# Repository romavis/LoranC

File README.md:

LORAN C (USSR "Chayka") receiver project
----

####Initial idea of project:
To build Loran-C navigational receiver with digital signal processing.  
Loran-C is (was?) a ground-based longwave navigational system working on frequency of 100 KHz, that was heavely used both by civilians and military prior to wide GPS adoption.

Receiver should also be able to lock onto signal of USSR "Chayka" system, similar to Loran-C, due to my location (nearest transmitter chain is "Chayka" GRI 8000)

####Licensed under:

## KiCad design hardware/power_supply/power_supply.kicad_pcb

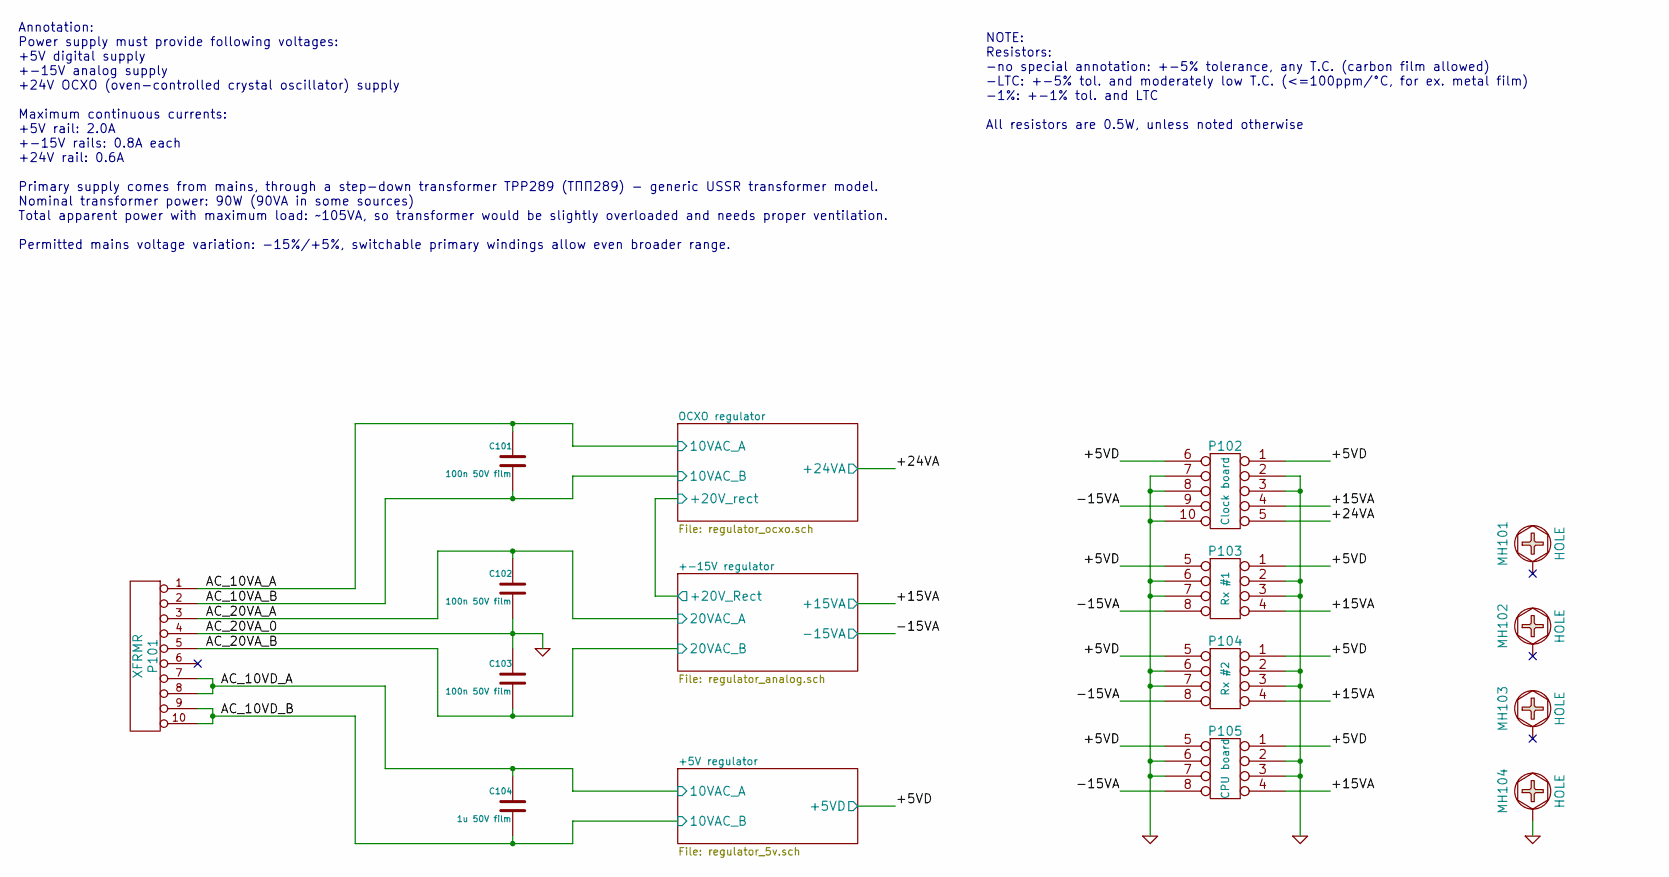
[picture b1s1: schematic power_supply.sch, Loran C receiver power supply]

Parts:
C101, C102, C103: 100n 50V film
C104: 1u 50V film
MH101, MH102, MH103, MH104: HOLE
P101: XFRMR
P102: Clock board
P103: Rx #1
P104: Rx #2
P105: CPU board

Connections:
/+5V regulator/10VAC_A: C104.1, P101.7, P101.8; also elsewhere on the board
/+5V regulator/10VAC_B: C104.2, P101.9, P101.10; also elsewhere on the board
/+5V regulator/+5VD: P102.1, P102.6, P103.1, P103.5, P104.1, P104.5, P105.1, P105.5; also elsewhere on the board
/+-15V regulator/20VAC_A: C102.1, P101.3; also elsewhere on the board
/+-15V regulator/20VAC_B: C103.2, P101.5; also elsewhere on the board
/+-15V regulator/+15VA: P102.4, P103.4, P104.4, P105.4; also elsewhere on the board
/+-15V regulator/-15VA: P102.9, P103.8, P104.8, P105.8; also elsewhere on the board
/OCXO regulator/10VAC_A: C101.1, P101.1; also elsewhere on the board
/OCXO regulator/10VAC_B: C101.2, P101.2; also elsewhere on the board
/OCXO regulator/+24VA: P102.5; also elsewhere on the board
GND: C102.2, C103.1, MH104.1, P101.4, P102.2, P102.3, P102.7, P102.8, P102.10, P103.2, P103.3, P103.6, P103.7, P104.2, P104.3, P104.6, P104.7, P105.2, P105.3, P105.6, P105.7; also elsewhere on the board

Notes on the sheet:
Annotation: Power supply must provide following voltages: +5V digital supply +-15V analog supply +24V OCXO (oven-controlled crystal oscillator) supply Maximum continuous currents: +5V rail: 2.0A +-15V rails: 0.8A each +24V rail: 0.6A Primary supply comes from mains, through a step-down transformer 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
NOTE: Resistors: -no special annotation: +-5% tolerance, any T.C. (carbon film allowed) -LTC: +-5% tol. and moderately low T.C. (<=100ppm/°C, for ex. metal film) -1%: +-1% tol. and LTC All resistors are 0.5W, unless noted otherwise

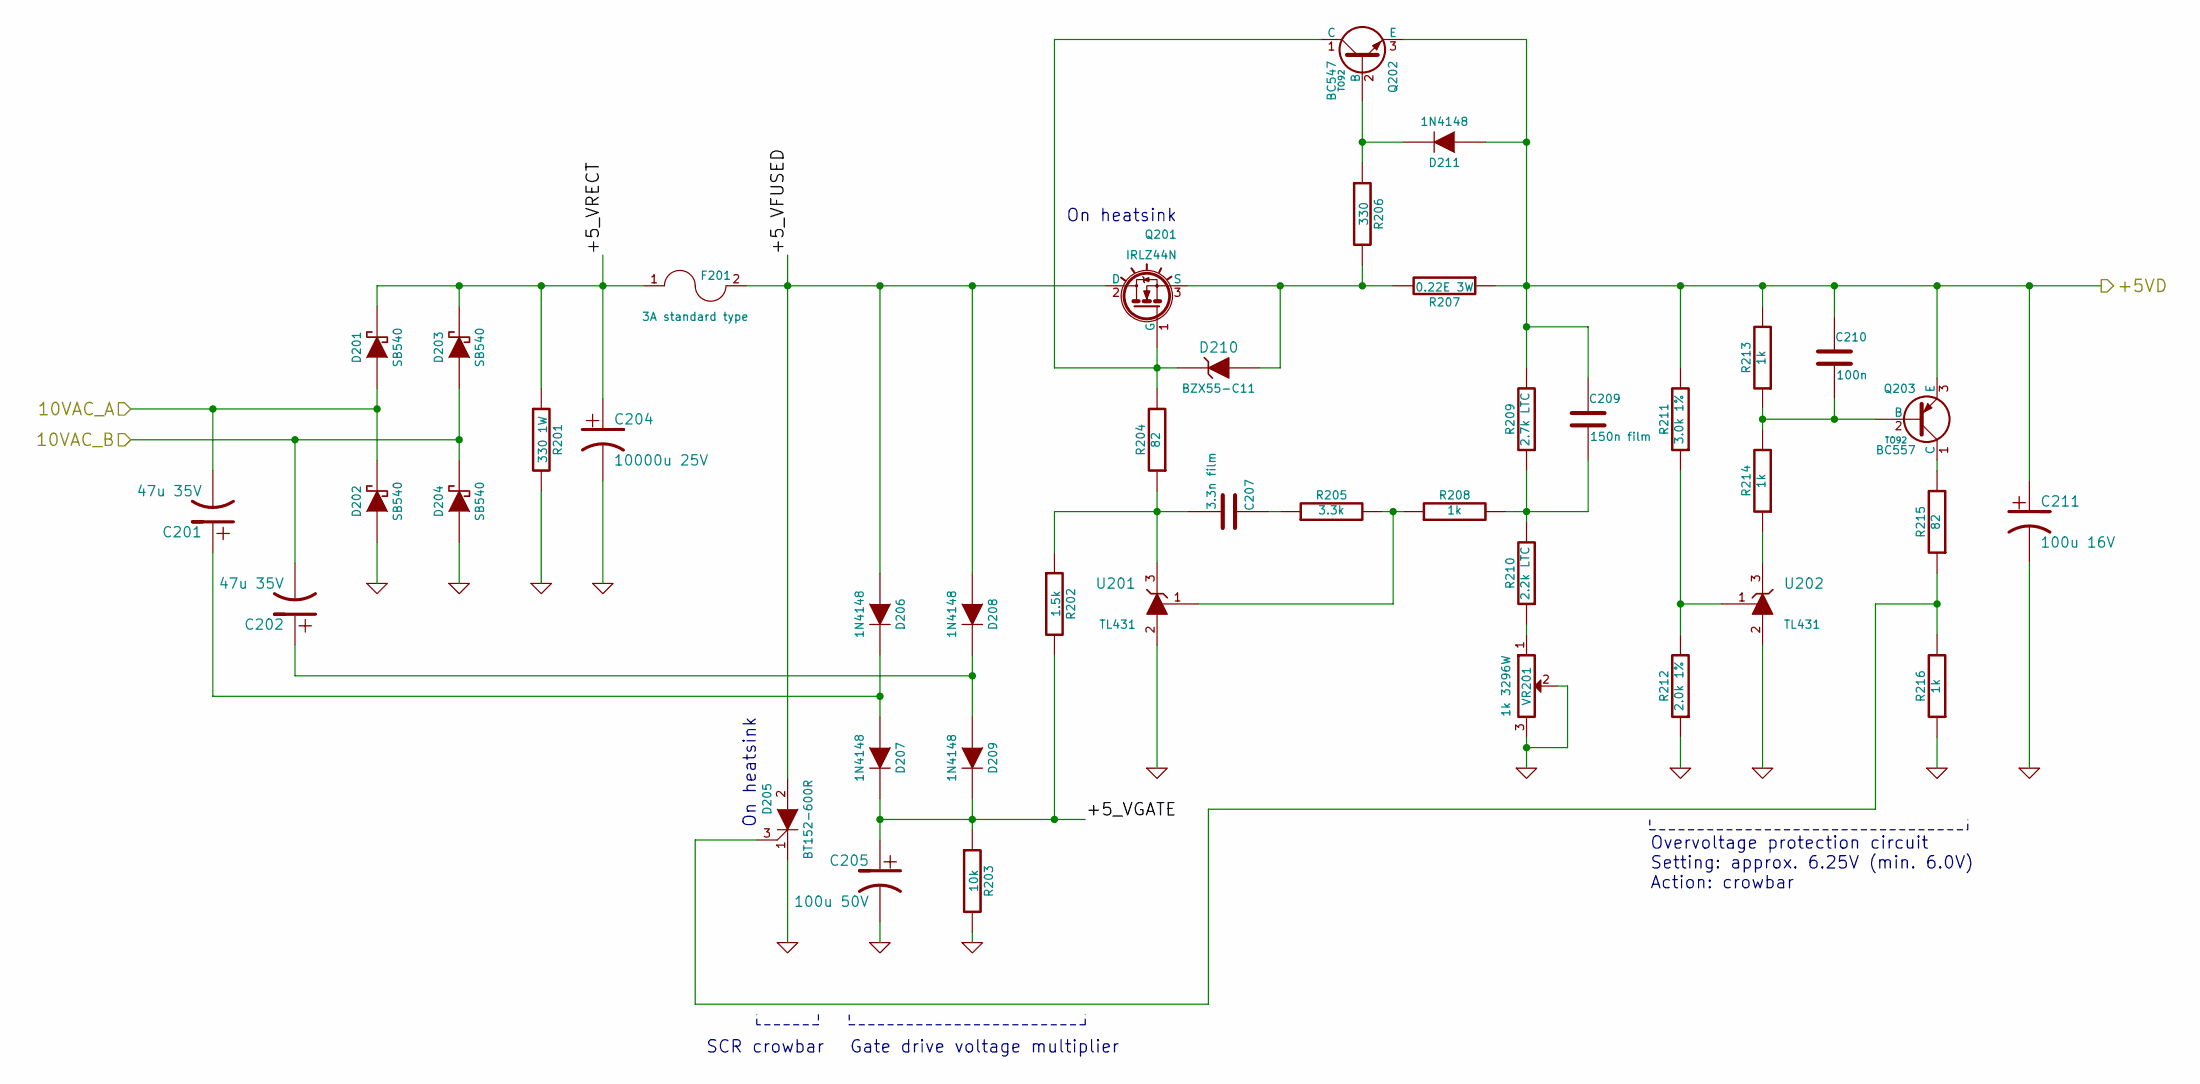
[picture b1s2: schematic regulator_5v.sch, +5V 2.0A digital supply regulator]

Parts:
C201, C202: 47u 35V
C204: 10000u 25V
C205: 100u 50V
C207: 3.3n film
C209: 150n film
C210: 100n
C211: 100u 16V
D201, D202, D203, D204: SB540
D205: BT152-600R
D206, D207, D208, D209, D211: 1N4148
D210: BZX55-C11
F201: 3A standard type
Q201: IRLZ44N
Q202: BC547; TO92
Q203: BC557; TO92
R201: 330 1W
R202: 1.5k
R203: 10k
R204, R215: 82
R205: 3.3k
R206: 330
R207: 0.22E 3W
R208, R213, R214, R216: 1k
R209: 2.7k LTC
R210: 2.2k LTC
R211: 3.0k 1%
R212: 2.0k 1%
U201, U202: TL431; TO92
VR201: 1k 3296W

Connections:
/+5V regulator/10VAC_A: C201.2, D201.1 (A), D202.2 (K); also elsewhere on the board
/+5V regulator/10VAC_B: C202.2, D203.1 (A), D204.2 (K); also elsewhere on the board
/+5V regulator/+5VD: C209.1, C210.1, C211.1, D211.1 (A), Q202.3 (E), Q203.3 (E), R207.1, R209.2, R211.2, R213.2; also elsewhere on the board
/+5V regulator/+5_VFUSED: D205.2 (A), D206.1 (A), D208.1 (A), F201.2, Q201.2 (D)
/+5V regulator/+5_VGATE: C205.1, D207.2 (K), D209.2 (K), R202.2, R203.1
/+5V regulator/+5_VRECT: C204.1, D201.2 (K), D203.2 (K), F201.1, R201.1
GND: C204.2, C205.2, C211.2, D202.1 (A), D204.1 (A), D205.1 (K), R201.2, R203.2, R212.1, R216.1, U201.2 (A), U202.2 (A), VR201.2, VR201.3; also elsewhere on the board
unnamed: C201.1, D206.2 (K), D207.1 (A)
unnamed: C202.1, D208.2 (K), D209.1 (A)
unnamed: C207.1, R205.1
unnamed: C207.2, R202.1, R204.1, U201.3 (K)
unnamed: C209.2, R208.2, R209.1, R210.2
unnamed: C210.2, Q203.2 (B), R213.1, R214.2
unnamed: D205.3 (G), R215.1, R216.2
unnamed: D210.1 (A), Q201.3 (S), R206.2, R207.2
unnamed: D210.2 (K), Q201.1 (G), Q202.1 (C), R204.2
unnamed: D211.2 (K), Q202.2 (B), R206.1
unnamed: Q203.1 (C), R215.2
unnamed: R205.2, R208.1, U201.1 (Ref)
unnamed: R210.1, VR201.1
unnamed: R211.1, R212.2, U202.1 (Ref)
unnamed: R214.1, U202.3 (K)

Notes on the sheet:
Overvoltage protection circuit Setting: approx. 6.25V (min. 6.0V) Action: crowbar
Gate drive voltage multiplier
SCR crowbar
On heatsink

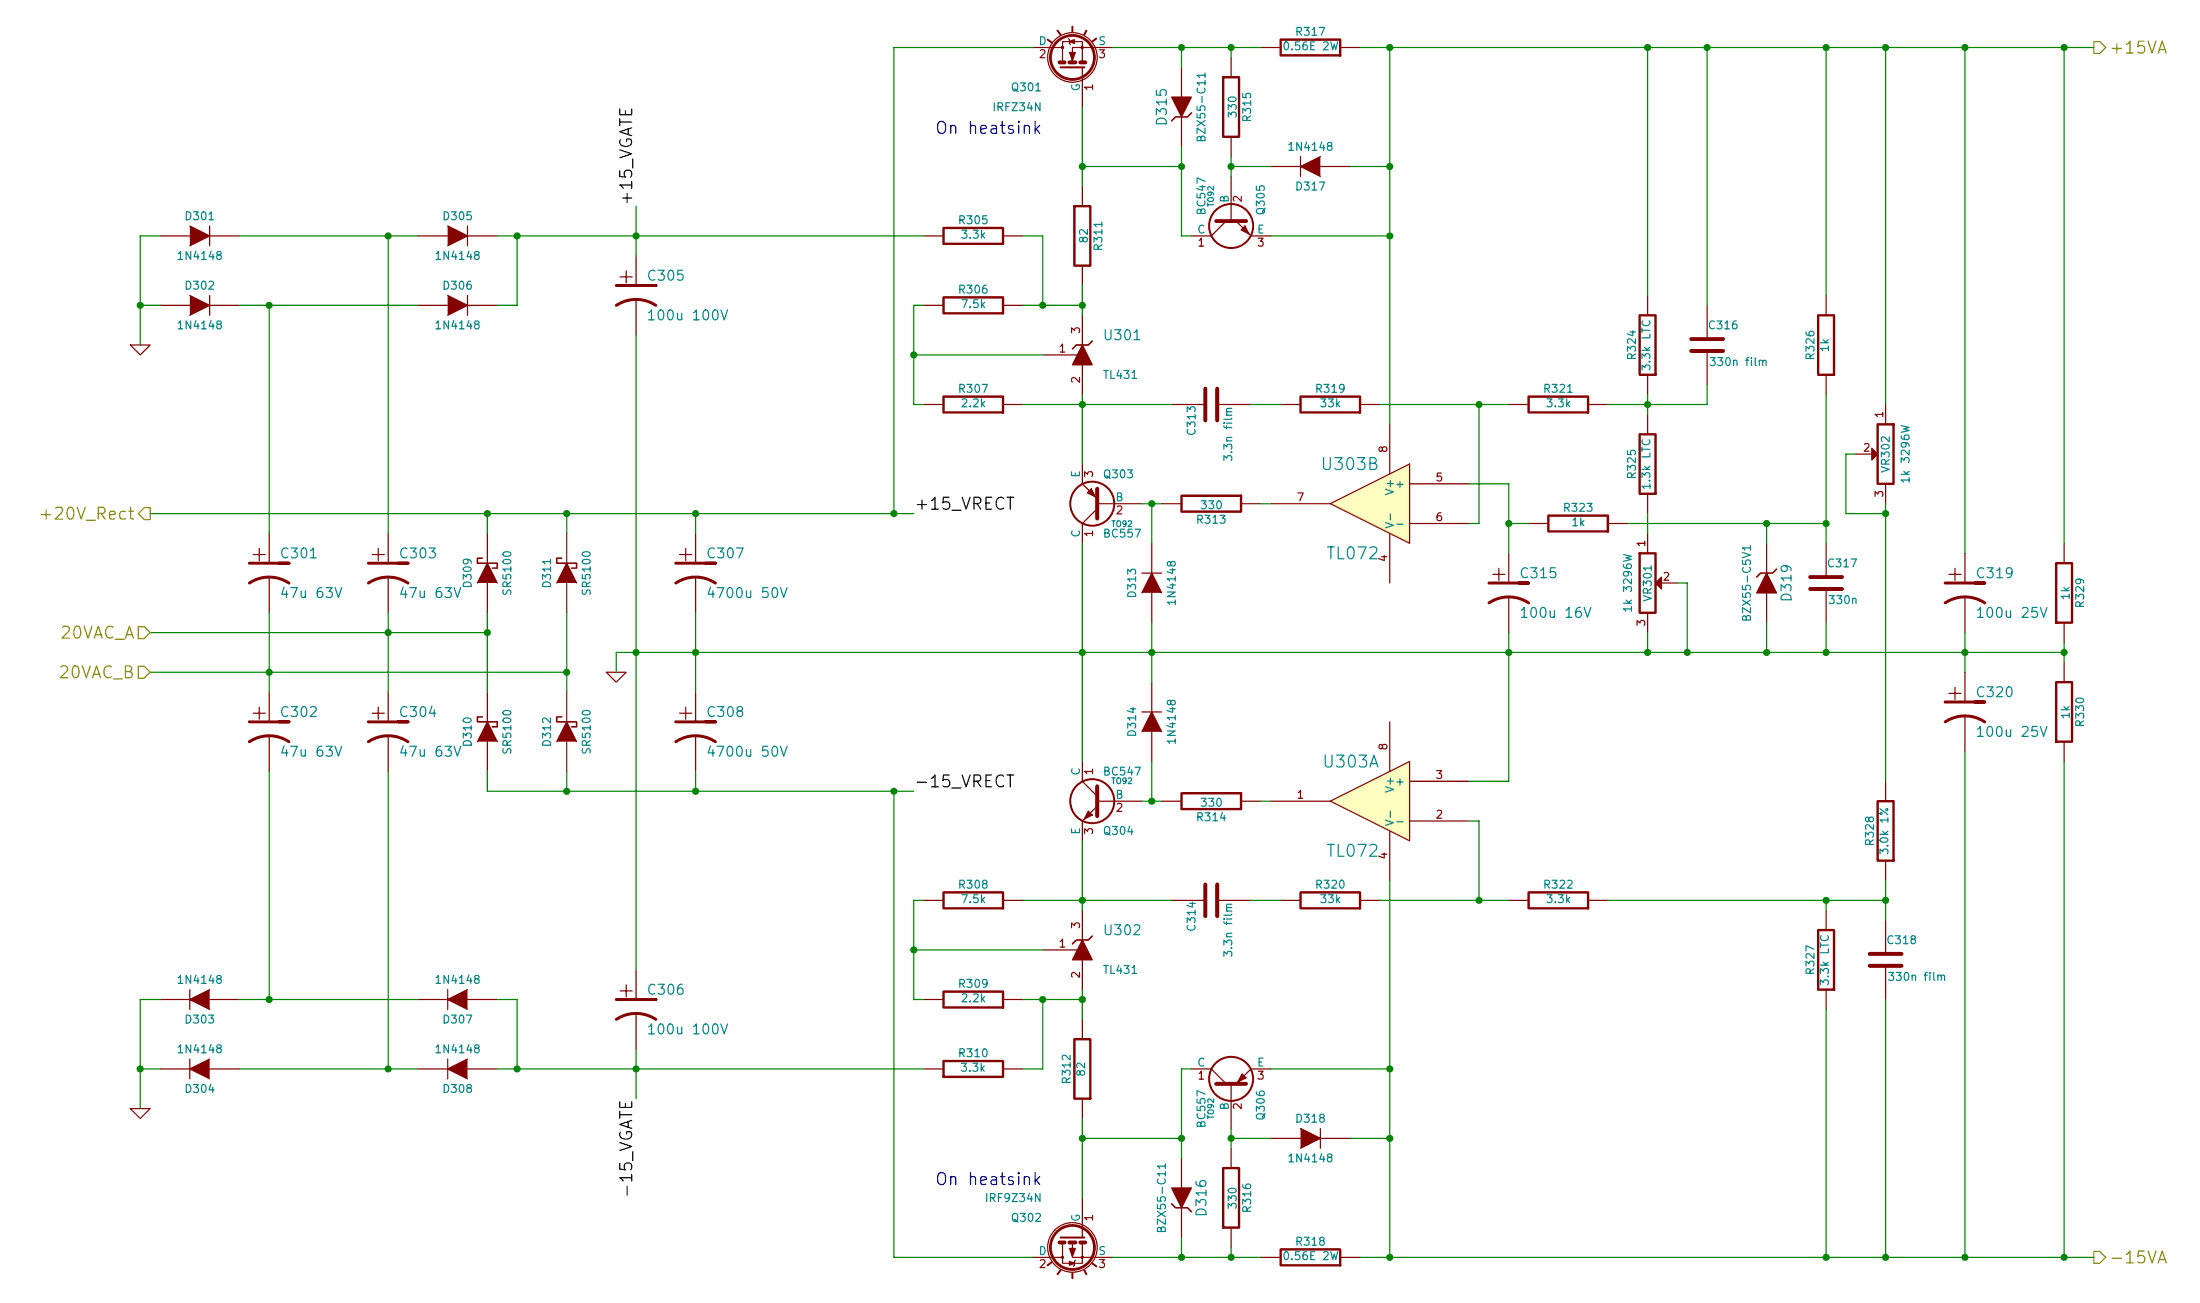
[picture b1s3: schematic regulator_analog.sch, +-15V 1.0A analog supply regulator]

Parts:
C301, C302, C303, C304: 47u 63V
C305, C306: 100u 100V
C307, C308: 4700u 50V
C313, C314: 3.3n film
C315: 100u 16V
C316, C318: 330n film
C317: 330n
C319, C320: 100u 25V
D301, D302, D303, D304, D305, D306, D307, D308, D313, D314, D317, D318: 1N4148
D309, D310, D311, D312: SR5100
D315, D316: BZX55-C11
D319: BZX55-C5V1
Q301: IRFZ34N
Q302: IRF9Z34N
Q303, Q306: BC557; TO92
Q304, Q305: BC547; TO92
R305, R310, R321, R322: 3.3k
R306, R308: 7.5k
R307, R309: 2.2k
R311, R312: 82
R313, R314, R315, R316: 330
R317, R318: 0.56E 2W
R319, R320: 33k
R323, R326, R329, R330: 1k
R324, R327: 3.3k LTC
R325: 1.3k LTC
R328: 3.0k 1%
U301, U302: TL431; TO92
U303: TL072
VR301, VR302: 1k 3296W

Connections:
/+-15V regulator/20VAC_A: C303.2, C304.1, D309.1 (A), D310.2 (K); also elsewhere on the board
/+-15V regulator/20VAC_B: C301.2, C302.1, D311.1 (A), D312.2 (K); also elsewhere on the board
/+-15V regulator/+15VA: C316.1, C319.1, D317.1 (A), Q305.3 (E), R317.1, R324.2, R326.2, R329.2, U303.8 (V+), VR302.1; also elsewhere on the board
/+-15V regulator/+15_VGATE: C305.1, D305.2 (K), D306.2 (K), R305.2
/+-15V regulator/+20V_Rect: C307.1, D309.2 (K), D311.2 (K), Q301.2 (D); also elsewhere on the board
/+-15V regulator/-15VA: C318.2, C320.2, D318.2 (K), Q306.3 (E), R318.1, R327.1, R330.1, U303.4 (V-); also elsewhere on the board
/+-15V regulator/-15_VGATE: C306.2, D307.1 (A), D308.1 (A), R310.1
/+-15V regulator/-15_VRECT: C308.2, D310.1 (A), D312.1 (A), Q302.2 (D)
GND: C305.2, C306.1, C307.2, C308.1, C315.2, C317.2, C319.2, C320.1, D301.1 (A), D302.1 (A), D303.2 (K), D304.2 (K), D313.1 (A), D314.2 (K), D319.1 (A), Q303.1 (C), Q304.1 (C), R329.1, R330.2, U303.3 (+), VR301.2, VR301.3; also elsewhere on the board
unnamed: C301.1, D302.2 (K), D306.1 (A)
unnamed: C302.2, D303.1 (A), D307.2 (K)
unnamed: C303.1, D301.2 (K), D305.1 (A)
unnamed: C304.2, D304.1 (A), D308.2 (K)
unnamed: C313.1, Q303.3 (E), R307.1, U301.2 (A)
unnamed: C313.2, R319.2
unnamed: C314.1, Q304.3 (E), R308.1, U302.3 (K)
unnamed: C314.2, R320.2
unnamed: C315.1, R323.2, U303.5 (+)
unnamed: C316.2, R321.1, R324.1, R325.2
unnamed: C317.1, D319.2 (K), R323.1, R326.1
unnamed: C318.1, R322.1, R327.2, R328.1
unnamed: D313.2 (K), Q303.2 (B), R313.2
unnamed: D314.1 (A), Q304.2 (B), R314.2
unnamed: D315.1 (A), Q301.3 (S), R315.1, R317.2
unnamed: D315.2 (K), Q301.1 (G), Q305.1 (C), R311.1
unnamed: D316.1 (A), Q302.1 (G), Q306.1 (C), R312.1
unnamed: D316.2 (K), Q302.3 (S), R316.1, R318.2
unnamed: D317.2 (K), Q305.2 (B), R315.2
unnamed: D318.1 (A), Q306.2 (B), R316.2
unnamed: R305.1, R306.1, R311.2, U301.3 (K)
unnamed: R306.2, R307.2, U301.1 (Ref)
unnamed: R308.2, R309.2, U302.1 (Ref)
unnamed: R309.1, R310.2, R312.2, U302.2 (A)
unnamed: R313.1, U303.7
unnamed: R314.1, U303.1
unnamed: R319.1, R321.2, U303.6 (-)
unnamed: R320.1, R322.2, U303.2 (-)
unnamed: R325.1, VR301.1
unnamed: R328.2, VR302.2, VR302.3

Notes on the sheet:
On heatsink

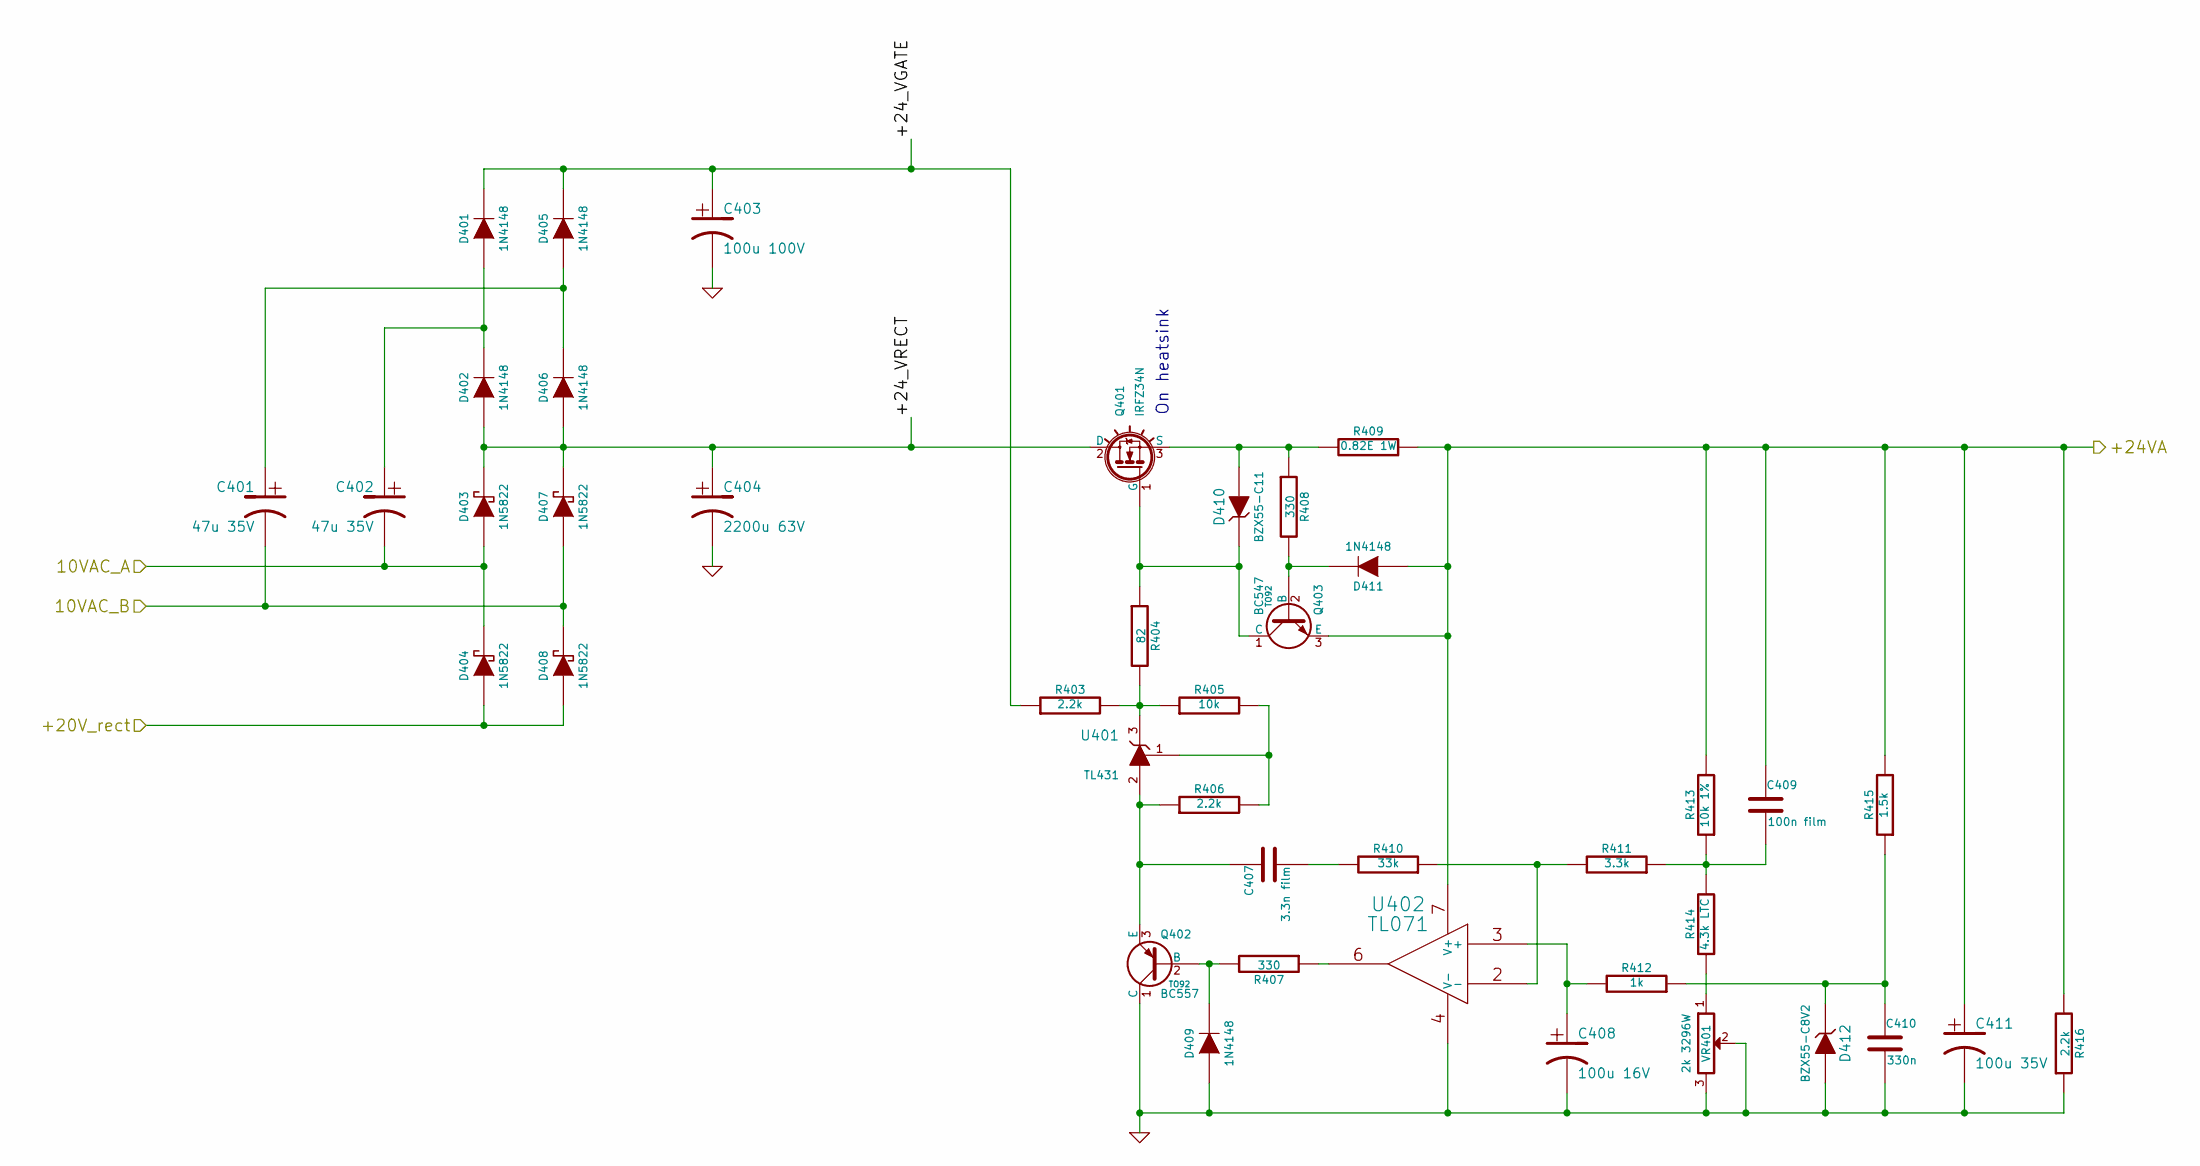
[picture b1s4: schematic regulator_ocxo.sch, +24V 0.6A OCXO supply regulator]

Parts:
C401, C402: 47u 35V
C403: 100u 100V
C404: 2200u 63V
C407: 3.3n film
C408: 100u 16V
C409: 100n film
C410: 330n
C411: 100u 35V
D401, D402, D405, D406, D409, D411: 1N4148
D403, D404, D407, D408: 1N5822
D410: BZX55-C11
D412: BZX55-C8V2
Q401: IRFZ34N
Q402: BC557; TO92
Q403: BC547; TO92
R403, R406, R416: 2.2k
R404: 82
R405: 10k
R407, R408: 330
R409: 0.82E 1W
R410: 33k
R411: 3.3k
R412: 1k
R413: 10k 1%
R414: 4.3k LTC
R415: 1.5k
U401: TL431; TO92
U402: TL071
VR401: 2k 3296W

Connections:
/+-15V regulator/+20V_Rect: D404.1 (A), D408.1 (A); also elsewhere on the board
/OCXO regulator/10VAC_A: C402.2, D403.1 (A), D404.2 (K); also elsewhere on the board
/OCXO regulator/10VAC_B: C401.2, D407.1 (A), D408.2 (K); also elsewhere on the board
/OCXO regulator/+24VA: C409.1, C411.1, D411.1 (A), Q403.3 (E), R409.1, R413.2, R415.2, R416.2, U402.7 (V+); also elsewhere on the board
/OCXO regulator/+24_VGATE: C403.1, D401.2 (K), D405.2 (K), R403.1
/OCXO regulator/+24_VRECT: C404.1, D402.1 (A), D403.2 (K), D406.1 (A), D407.2 (K), Q401.2 (D)
GND: C403.2, C404.2, C408.2, C410.2, C411.2, D409.1 (A), D412.1 (A), Q402.1 (C), R416.1, U402.4 (V-), VR401.2, VR401.3; also elsewhere on the board
unnamed: C401.1, D405.1 (A), D406.2 (K)
unnamed: C402.1, D401.1 (A), D402.2 (K)
unnamed: C407.1, Q402.3 (E), R406.1, U401.2 (A)
unnamed: C407.2, R410.2
unnamed: C408.1, R412.2, U402.3 (+)
unnamed: C409.2, R411.1, R413.1, R414.2
unnamed: C410.1, D412.2 (K), R412.1, R415.1
unnamed: D409.2 (K), Q402.2 (B), R407.2
unnamed: D410.1 (A), Q401.3 (S), R408.1, R409.2
unnamed: D410.2 (K), Q401.1 (G), Q403.1 (C), R404.1
unnamed: D411.2 (K), Q403.2 (B), R408.2
unnamed: R403.2, R404.2, R405.1, U401.3 (K)
unnamed: R405.2, R406.2, U401.1 (Ref)
unnamed: R407.1, U402.6
unnamed: R410.1, R411.2, U402.2 (-)
unnamed: R414.1, VR401.1

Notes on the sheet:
On heatsink

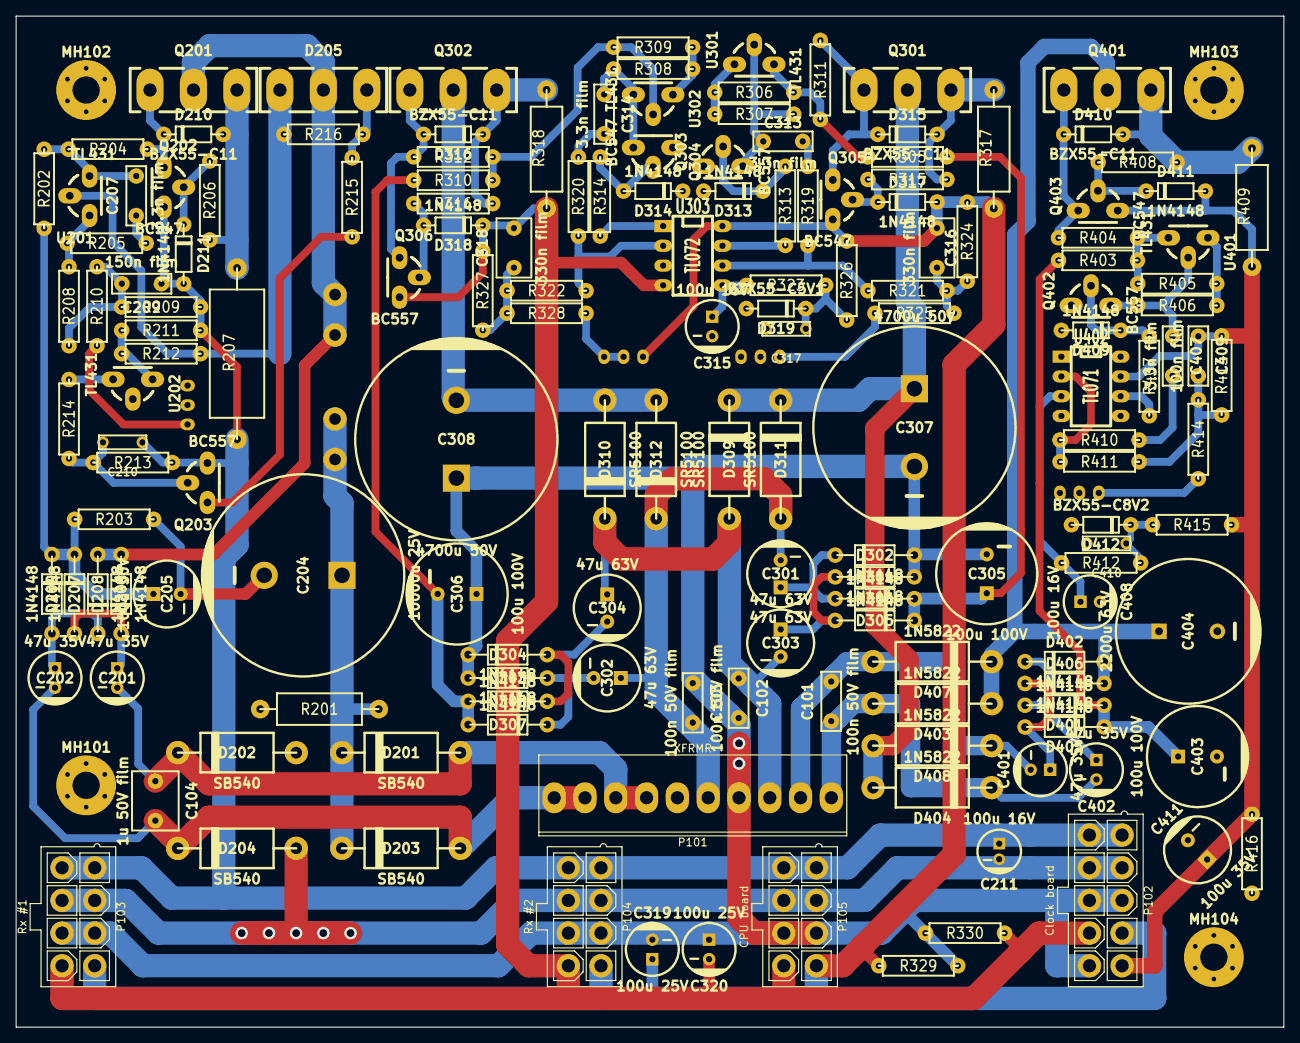
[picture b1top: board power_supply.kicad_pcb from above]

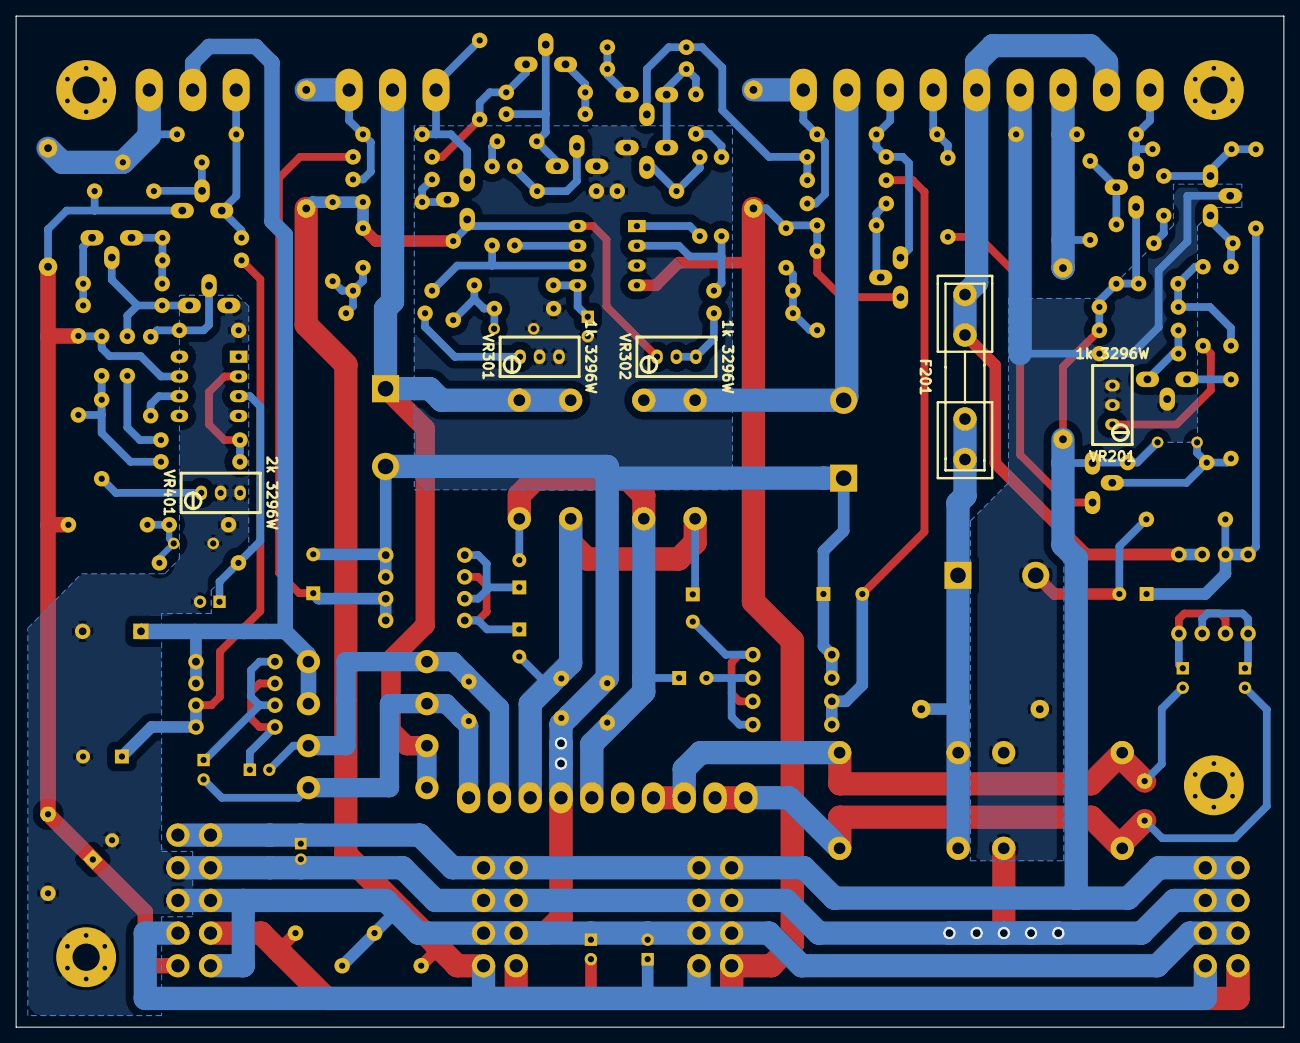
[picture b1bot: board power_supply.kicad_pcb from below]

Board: 2 copper layers, 163.0 x 130.0 mm, 168 parts (5 on the bottom side), 81 nets.

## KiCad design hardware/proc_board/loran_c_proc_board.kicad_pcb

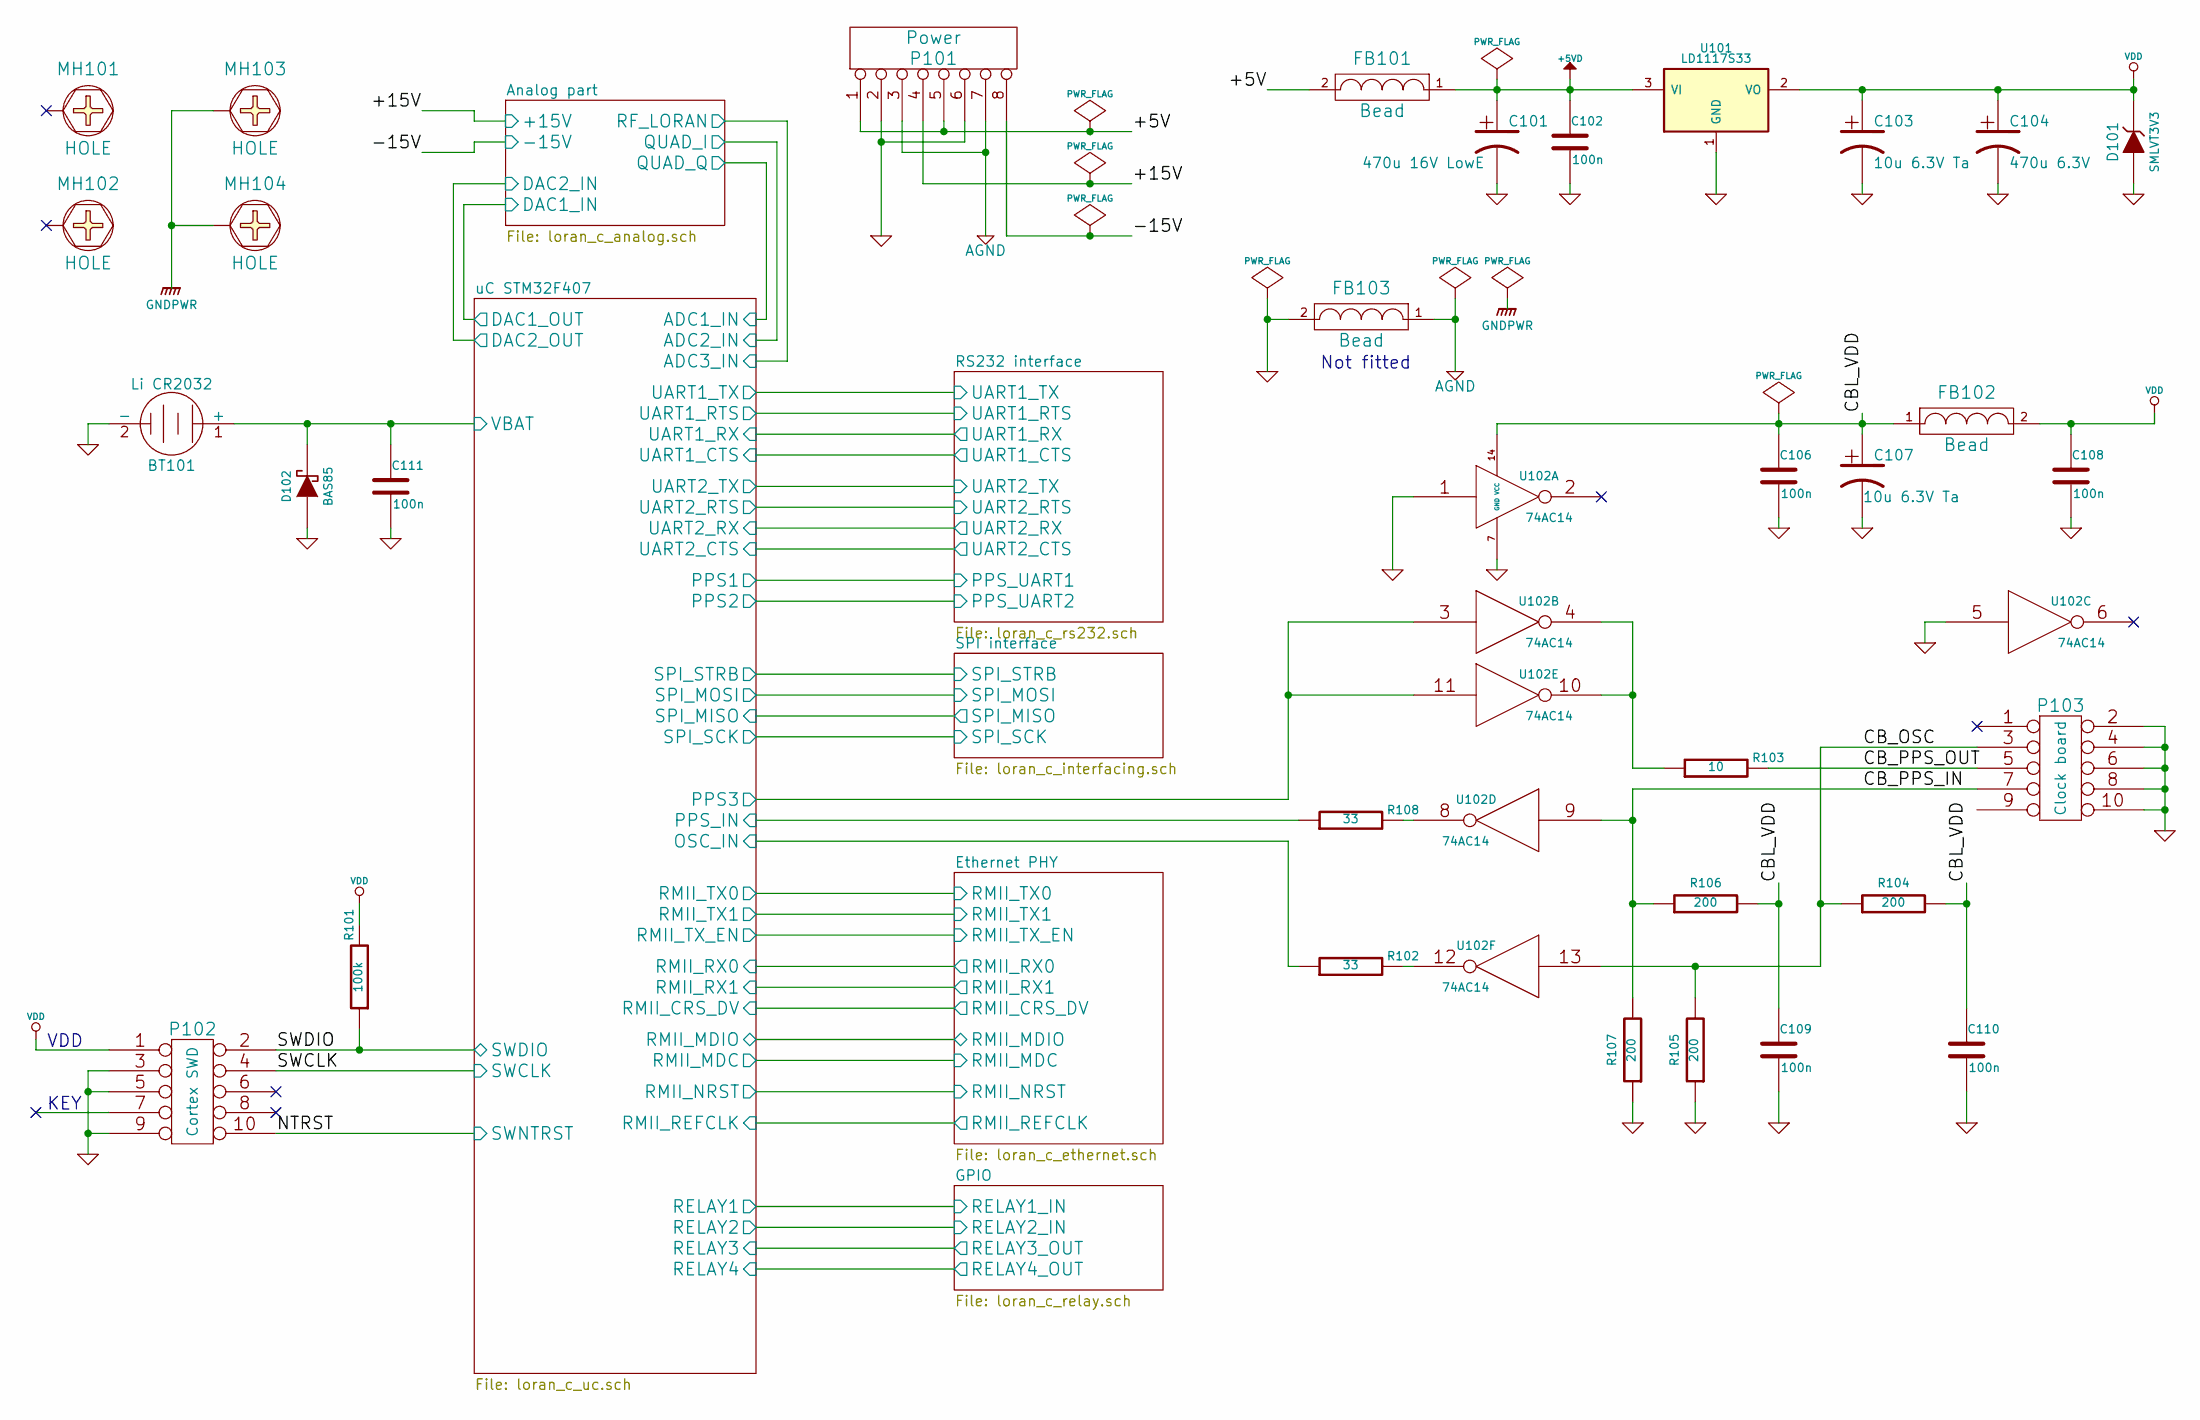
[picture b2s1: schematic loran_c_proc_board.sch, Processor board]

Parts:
BT101: Li CR2032; bh840
C101: 470u 16V LowE; CP_10x12.5mm
C102, C106, C108, C109, C110: 100n; c_1206
C103, C107: 10u 6.3V Ta; c_tant_B
C104: 470u 6.3V; CP_6.3x11mm
C111: 100n; c_0805
D101: SMLVT3V3; do214aa
D102: BAS85; sod80c
FB101: Bead; RC07
FB102: Bead; rc07_vert
FB103: Bead; SM1812E
MH101, MH102, MH103, MH104: HOLE; Hole_3-5mm
P101: Power; minifit-8
P102: Cortex SWD; vasch_strip_5x2
P103: Clock board; vasch_strip_5x2
R101: 100k; r_1206
R102, R108: 33; r_1206
R103: 10; r_1206
R104, R105, R106, R107: 200; r_1206
U101: LD1117S33; TO-220_Neutral123_Vertical
U102: 74AC14; so-14

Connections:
+5VD: C101.1, C102.1, FB101.1, U101.3 (VI); also elsewhere on the board
/+5V: FB101.2, P101.1, P101.5
/Analog part/+15V: P101.4; also elsewhere on the board
/Analog part/-15V: P101.8; also elsewhere on the board
/CBL_VDD: C106.1, C107.1, C109.1, C110.1, FB102.1, R104.2, R106.2, U102.14 (VCC)
/CB_OSC: P103.3, R104.1, R105.2, U102.13
/CB_PPS_IN: P103.7, R106.1, R107.2, U102.9
/CB_PPS_OUT: P103.5, R103.2
/uC STM32F407/OSC_IN: R102.1; also elsewhere on the board
/uC STM32F407/PPS3: U102.3, U102.11; also elsewhere on the board
/uC STM32F407/PPS_IN: R108.1; also elsewhere on the board
/uC STM32F407/SWCLK: P102.4; also elsewhere on the board
/uC STM32F407/SWDIO: P102.2, R101.1; also elsewhere on the board
/uC STM32F407/SWNTRST: P102.10; also elsewhere on the board
/uC STM32F407/VBAT: BT101.1 (+), C111.1, D102.2 (K); also elsewhere on the board
AGND: FB103.1, P101.3, P101.7; also elsewhere on the board
GND: BT101.2 (-), C101.2, C102.2, C103.2, C104.2, C106.2, C107.2, C108.2, C109.2, C110.2, C111.2, D101.1 (A), D102.1 (A), FB103.2, P101.2, P101.6, P102.3, P102.5, P102.9, P103.2, P103.4, P103.6, P103.8, P103.10, R105.1, R107.1, U101.1 (GND), U102.1, U102.5, U102.7 (GND); also elsewhere on the board
GNDPWR: MH103.1, MH104.1; also elsewhere on the board
unnamed: R102.2, U102.12
unnamed: R103.1, U102.4, U102.10
unnamed: R108.2, U102.8
VDD: C103.1, C104.1, C108.1, D101.2 (K), FB102.2, P102.1, R101.2, U101.2 (VO); also elsewhere on the board

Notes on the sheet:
KEY
VDD
Not fitted

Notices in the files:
hardware/proc_board/loran_c_proc_board.kicad_pcb:
© 2014
